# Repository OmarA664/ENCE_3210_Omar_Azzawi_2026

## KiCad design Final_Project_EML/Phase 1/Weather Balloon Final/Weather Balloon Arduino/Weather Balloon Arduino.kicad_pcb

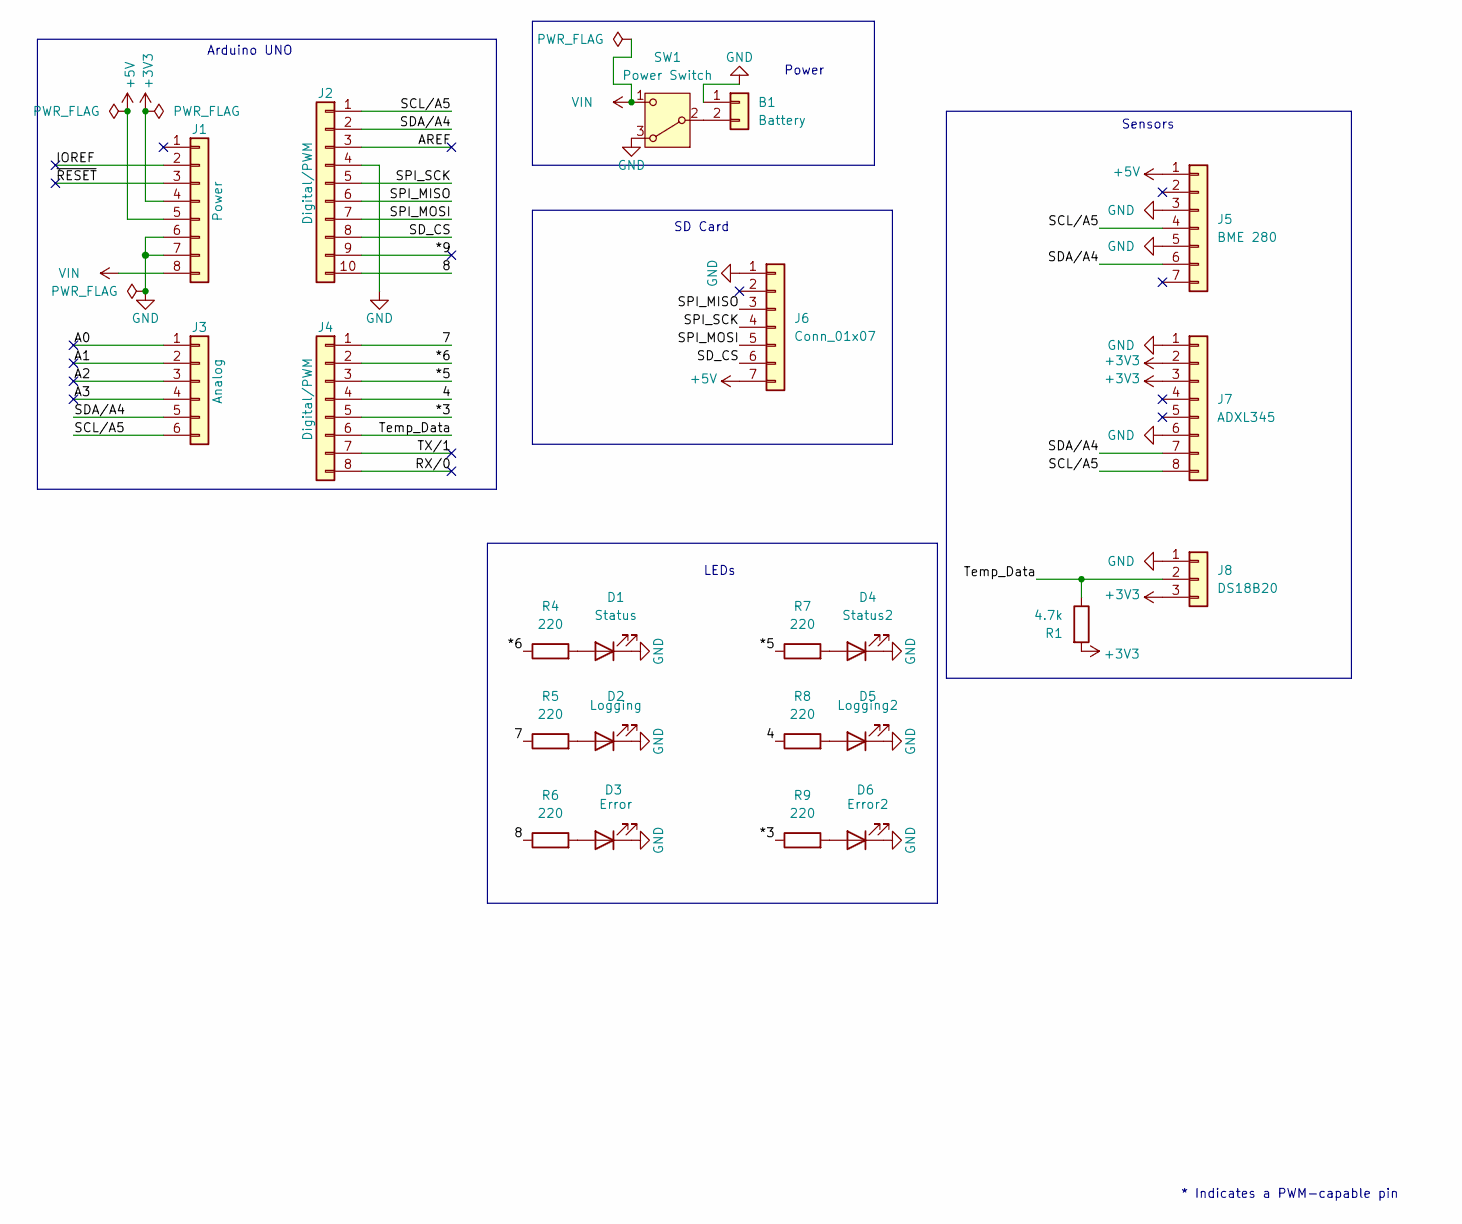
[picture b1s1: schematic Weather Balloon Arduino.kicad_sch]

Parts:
B1: Battery; PinHeader_1x02_P2.54mm_Vertical
D1: Status; LED_D5.0mm
D2: Logging; LED_D5.0mm
D3: Error; LED_D5.0mm
D4: Status2; LED_D5.0mm
D5: Logging2; LED_D5.0mm
D6: Error2; LED_D5.0mm
J1: Power; PinSocket_1x08_P2.54mm_Vertical
J2: Digital/PWM; PinSocket_1x10_P2.54mm_Vertical
J3: Analog; PinSocket_1x06_P2.54mm_Vertical
J4: Digital/PWM; PinSocket_1x08_P2.54mm_Vertical
J5: BME 280; PinHeader_1x07_P2.54mm_Vertical_V2
J6: Conn_01x07; PinHeader_1x07_P2.54mm_Vertical
J7: ADXL345; PinSocket_1x08_P2.54mm_Vertical
J8: DS18B20; PinHeader_1x03_P2.54mm_Vertical
R1: 4.7k; R_Axial_DIN0204_L3.6mm_D1.6mm_P1.90mm_Vertical
R4, R5, R6, R7, R8, R9: 220; R_Axial_DIN0204_L3.6mm_D1.6mm_P1.90mm_Vertical
SW1: Power Switch; SW_Slide-03_Wuerth-WS-SLTV_10x2.5x6.4_P2.54mm

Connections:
+3V3: J1.4, J7.2, J7.3, J8.3, R1.2
+5V: J1.5, J5.1, J6.7
/4: J4.4, R8.1
/7: J4.1, R5.1
/8: J2.10, R6.1
/*3: J4.5, R9.1
/*5: J4.3, R7.1
/*6: J4.2, R4.1
/*9: J2.9
/A0: J3.1
/A1: J3.2
/A2: J3.3
/A3: J3.4
/AREF: J2.3
/IOREF: J1.2
/RX/0: J4.8
/SCL/A5: J2.1, J3.6, J5.4, J7.8
/SDA/A4: J2.2, J3.5, J5.6, J7.7
/SD_CS: J2.8, J6.6
/SPI_MISO: J2.6, J6.3
/SPI_MOSI: J2.7, J6.5
/SPI_SCK: J2.5, J6.4
/TX/1: J4.7
/Temp_Data: J4.6, J8.2, R1.1
/~RESET: J1.3
GND: B1.1, D1.1 (K), D2.1 (K), D3.1 (K), D4.1 (K), D5.1 (K), D6.1 (K), J1.6, J1.7, J2.4, J5.3, J5.5, J6.1, J7.1, J7.6, J8.1, SW1.3 (A)
unnamed: B1.2, SW1.2 (B)
unnamed: D1.2 (A), R4.2
unnamed: D2.2 (A), R5.2
unnamed: D3.2 (A), R6.2
unnamed: D4.2 (A), R7.2
unnamed: D5.2 (A), R8.2
unnamed: D6.2 (A), R9.2
VIN: J1.8, SW1.1 (C)

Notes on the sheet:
LEDs
Sensors
Arduino UNO
SD Card
* Indicates a PWM-capable pin
Power

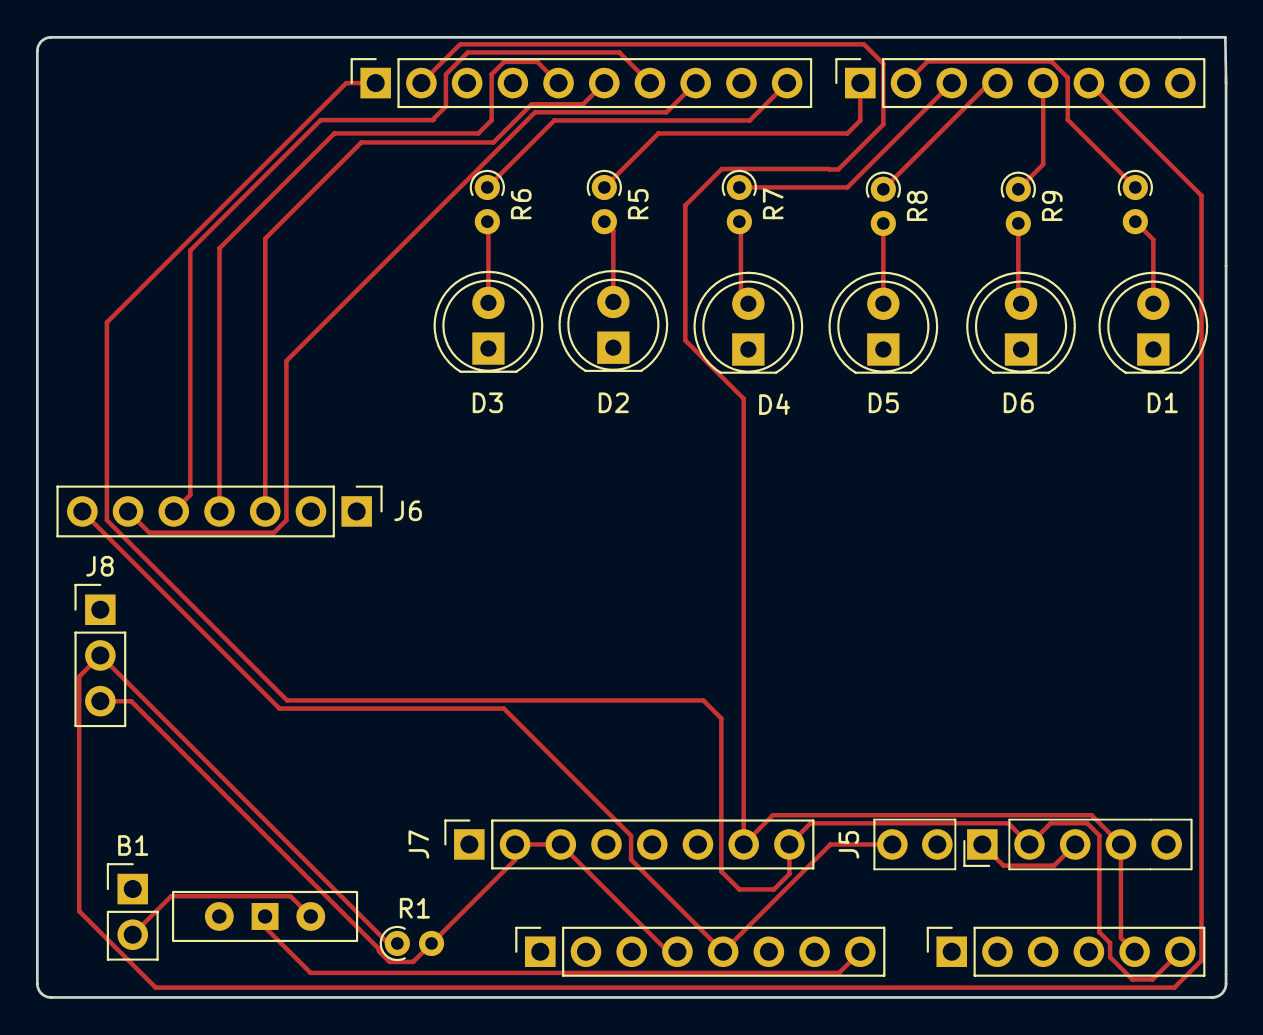
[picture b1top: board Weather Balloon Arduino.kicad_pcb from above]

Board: 2 copper layers, 66.0 x 53.3 mm, 23 parts (0 on the bottom side), 24 nets.

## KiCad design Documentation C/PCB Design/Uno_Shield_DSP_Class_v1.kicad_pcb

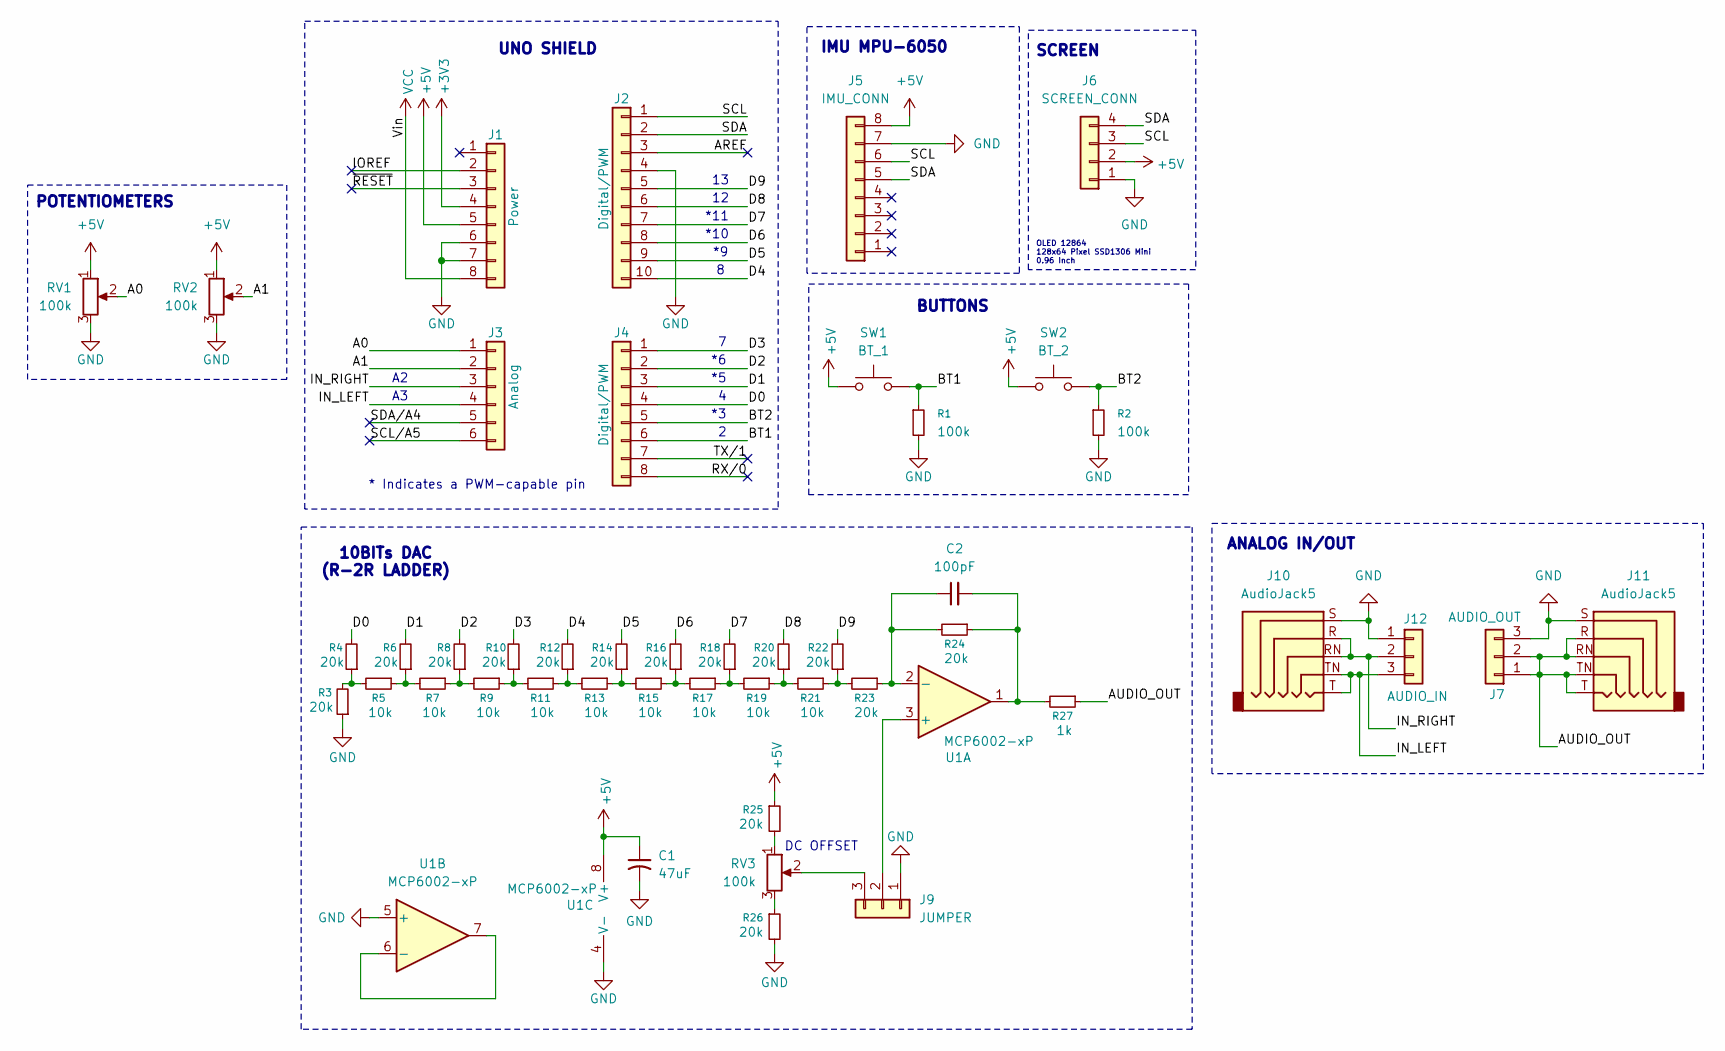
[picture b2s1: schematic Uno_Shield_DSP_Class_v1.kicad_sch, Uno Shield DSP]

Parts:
C1: 47uF; CP_Radial_D8.0mm_P2.50mm
C2: 100pF; C_Disc_D5.0mm_W2.5mm_P2.50mm
J1: Power; PinSocket_1x08_P2.54mm_Vertical
J2: Digital/PWM; PinSocket_1x10_P2.54mm_Vertical
J3: Analog; PinSocket_1x06_P2.54mm_Vertical
J4: Digital/PWM; PinSocket_1x08_P2.54mm_Vertical
J5: IMU_CONN; PinSocket_1x08_P2.54mm_Vertical
J6: SCREEN_CONN; PinHeader_1x04_P2.54mm_Vertical
J7: AUDIO_OUT; PinHeader_1x03_P2.54mm_Vertical
J9: JUMPER; PinHeader_1x03_P2.54mm_Vertical
J10, J11: AudioJack5; Jack_3.5mm_CUI_SJ1-3525N_Horizontal
J12: AUDIO_IN; PinHeader_1x03_P2.54mm_Vertical
R1, R2: 100k; R_Axial_DIN0309_L9.0mm_D3.2mm_P2.54mm_Vertical
R3, R4, R6, R8, R10, R12, R14, R16, R18, R20, R22, R23, R24, R25, R26: 20k; R_Axial_DIN0309_L9.0mm_D3.2mm_P2.54mm_Vertical
R5, R7, R9, R11, R13, R15, R17, R19, R21: 10k; R_Axial_DIN0309_L9.0mm_D3.2mm_P2.54mm_Vertical
R27: 1k; R_Axial_DIN0309_L9.0mm_D3.2mm_P2.54mm_Vertical
RV1, RV2, RV3: 100k; Potentiometer_Bourns_3386P_Vertical
SW1: BT_1; SW_PUSH_6mm
SW2: BT_2; SW_PUSH_6mm
U1: MCP6002-xP; DIP-8_W7.62mm_Socket_LongPads

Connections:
+3V3: J1.4
+5V: C1.1, J1.5, J5.8, J6.2, R25.1, RV1.1, RV2.1, SW1.1, SW2.1, U1.8 (V+)
/A0: J3.1, RV1.2
/A1: J3.2, RV2.2
/AREF: J2.3
/AUDIO_OUT: J7.1, J7.2, J11.R, J11.RN, J11.T, J11.TN, R27.1
/BT1: J4.6, R1.1, SW1.2
/BT2: J4.5, R2.1, SW2.2
/D0: J4.4, R4.2
/D1: J4.3, R6.2
/D2: J4.2, R8.2
/D3: J4.1, R10.2
/D4: J2.10, R12.2
/D5: J2.9, R14.2
/D6: J2.8, R16.2
/D7: J2.7, R18.2
/D8: J2.6, R20.2
/D9: J2.5, R22.2
/IN_LEFT: J3.4, J10.T, J10.TN, J12.3
/IN_RIGHT: J3.3, J10.R, J10.RN, J12.2
/IOREF: J1.2
/RX/0: J4.8
/SCL: J2.1, J5.6, J6.3
/SCL/A5: J3.6
/SDA: J2.2, J5.5, J6.4
/SDA/A4: J3.5
/TX/1: J4.7
/~RESET: J1.3
GND: C1.2, J1.6, J1.7, J2.4, J5.7, J6.1, J7.3, J9.1, J10.S, J11.S, J12.1, R1.2, R2.2, R3.1, R26.2, RV1.3, RV2.3, U1.4 (V-), U1.5 (+)
unnamed: C2.2, R24.1, R27.2, U1.1
unnamed: J9.2, U1.3 (+)
unnamed: J9.3, RV3.2
unnamed: R3.2, R4.1, R5.2
unnamed: R5.1, R6.1, R7.2
unnamed: R7.1, R8.1, R9.2
unnamed: R9.1, R10.1, R11.2
unnamed: R11.1, R12.1, R13.2
unnamed: R13.1, R14.1, R15.2
unnamed: R15.1, R16.1, R17.2
unnamed: R17.1, R18.1, R19.2
unnamed: R19.1, R20.1, R21.2
unnamed: R21.1, R22.1, R23.2
unnamed: R25.2, RV3.1
unnamed: R26.1, RV3.3
unnamed: C2.1, R23.1, R24.2, U1.2 (-)
unnamed: U1.6 (-), U1.7
VCC: J1.8

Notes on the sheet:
BUTTONS
IMU MPU-6050
POTENTIOMETERS
*11
DC OFFSET
10BITs DAC (R-2R LADDER)
ANALOG IN/OUT
*10
OLED 12864 128x64 Pixel SSD1306 Mini 0.96 Inch
* Indicates a PWM-capable pin
SCREEN
UNO SHIELD

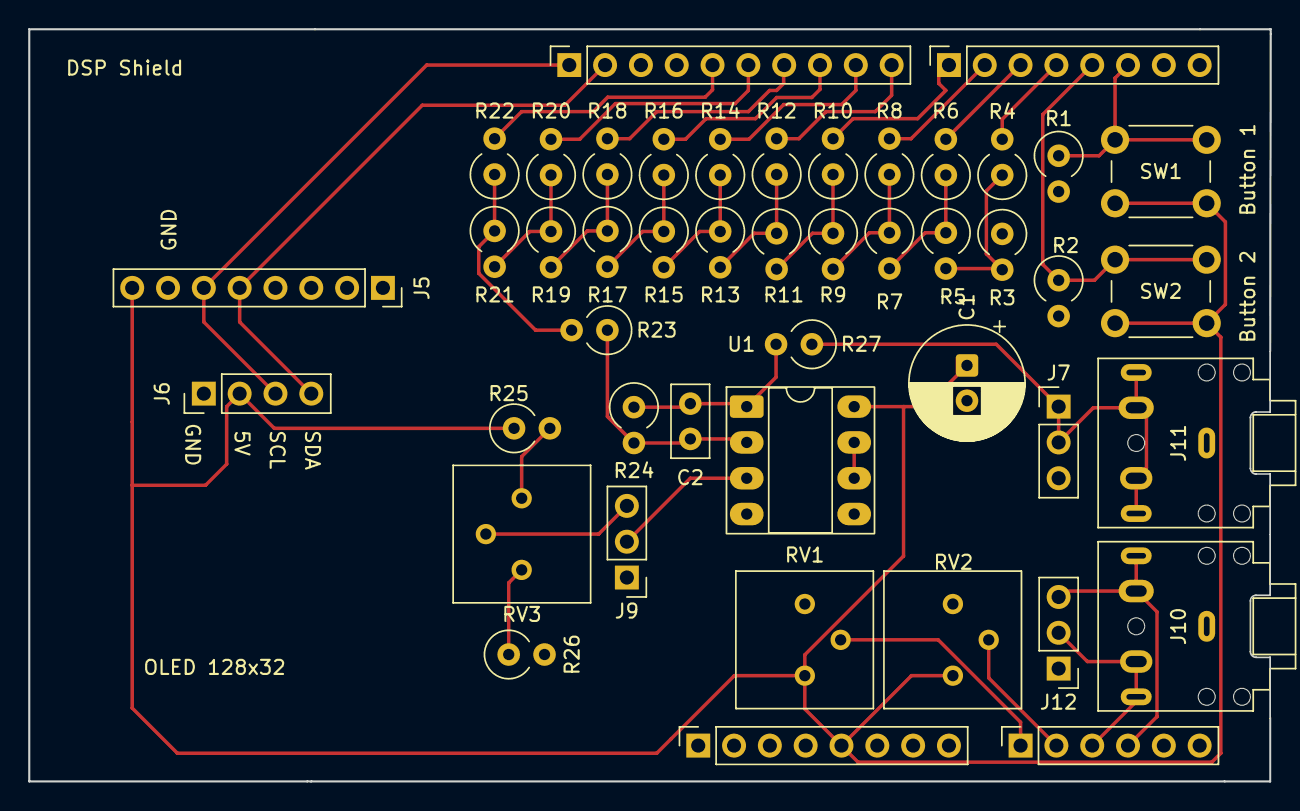
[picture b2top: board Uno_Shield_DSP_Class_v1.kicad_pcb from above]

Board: 2 copper layers, 88.0 x 53.3 mm, 46 parts (0 on the bottom side), 38 nets.

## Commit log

2026-01-09 test file
2026-01-11 C workshop
2026-01-11 Add files via upload
    code done in c workshop
2026-01-16 Create Lab 1
2026-01-16 Create READ ME
2026-03-09 Create Final_Project_EML
